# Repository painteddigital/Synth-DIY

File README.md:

# Synth-DIY
Files to produce the circuits to produce the instruments to produce sweet sweet music.

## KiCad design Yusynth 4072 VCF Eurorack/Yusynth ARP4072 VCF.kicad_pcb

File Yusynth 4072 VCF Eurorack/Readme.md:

This repo isn't quite production ready. So don't send these boards off to get made unless you know what you're doing. The jacks are not currently routed properly but I hope to fix them. If you know how to use KiCad and can fix them up, by all means submit a PR.

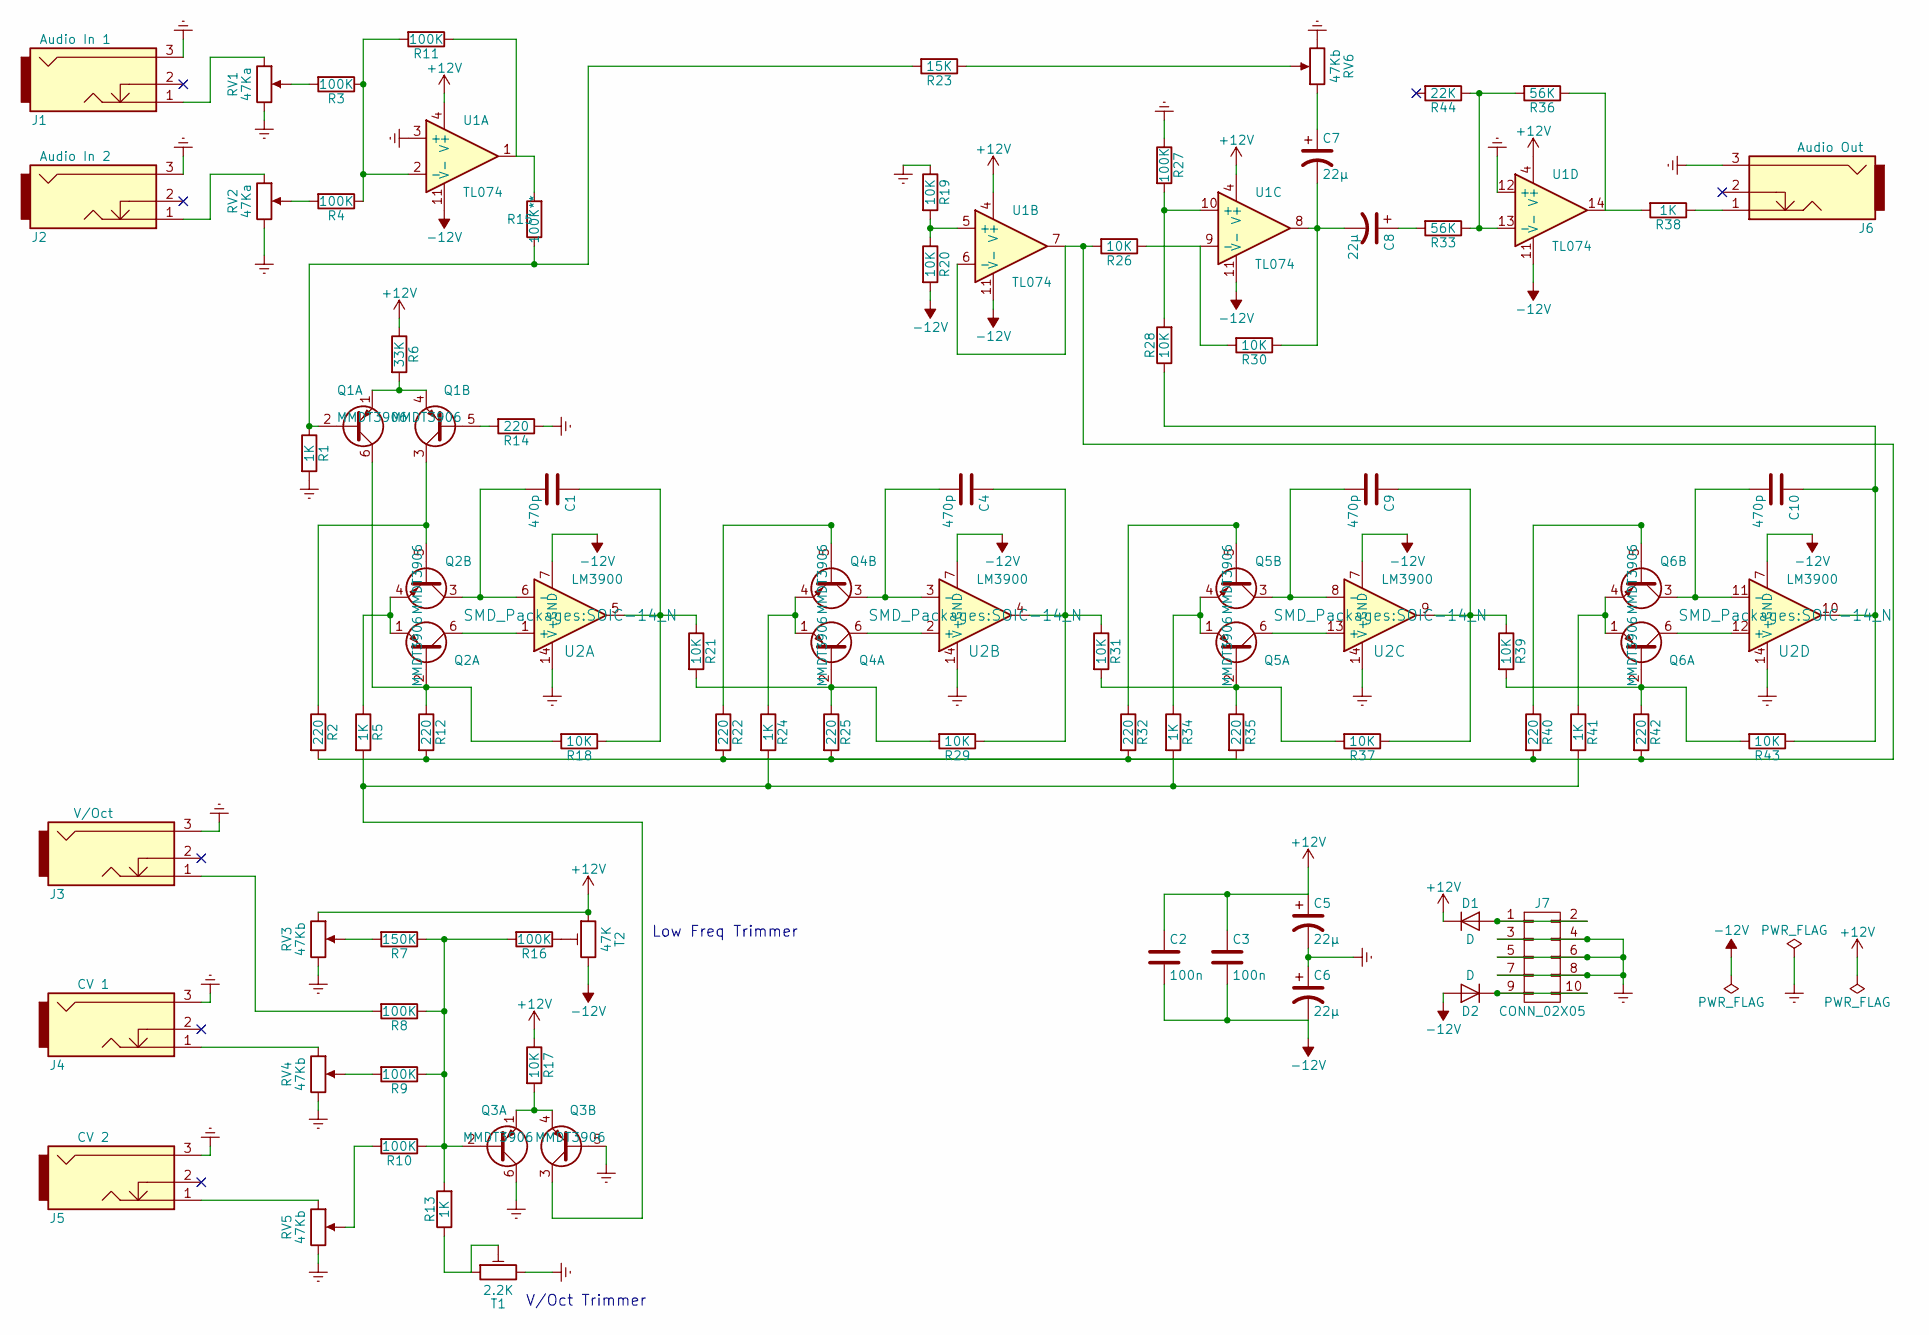
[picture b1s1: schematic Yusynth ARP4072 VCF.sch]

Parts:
C1, C4, C9, C10: 470p; C_Rect_L7.2mm_W4.5mm_P5.00mm_FKS2_FKP2_MKS2_MKP2
C2, C3: 100n; C_0603
C5, C6, C7, C8: 22µ; CP_Elec_5x5.7
D1, D2: D; D_SOD-123
J1: Audio In 1; THONKICONN
J2: Audio In 2; THONKICONN
J3: V/Oct; THONKICONN
J4: CV 1; THONKICONN
J5: CV 2; THONKICONN
J6: Audio Out; THONKICONN
J7: CONN_02X05; Pin_Header_Straight_2x05_Pitch2.54mm
Q1, Q2, Q3, Q4, Q5, Q6: MMDT3906; SOT-363_SC-70-6
R1, R5, R13, R24, R34, R38, R41: 1K; R_0603
R2, R12, R14, R22, R25, R32, R35, R40, R42: 220; R_0603
R3, R4, R8, R9, R10, R11, R16, R27: 100K; R_0603
R6: 33K; R_0603
R7: 150K; R_0603
R15: 100K**; R_0603
R17, R18, R19, R20, R21, R26, R28, R29, R30, R31, R37, R39, R43: 10K; R_0603
R23: 15K; R_0603
R33, R36: 56K; R_0603
R44: 22K; R_0603
RV1, RV2: 47Ka; Potentiometer_Alps_RK09L_Sleve_Single_Horizontal
RV3, RV4, RV5, RV6: 47Kb; Potentiometer_Alps_RK09L_Sleve_Single_Horizontal
T1: 2.2K; Potentiometer_Trimmer_Bourns_3296W
T2: 47K; Potentiometer_Trimmer_Bourns_3296W
U1: TL074; SOIC-14_N
U2: LM3900; SOIC-14_N

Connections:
+12V: C2.1, C3.1, C5.1, D1.1 (K), R6.1, R17.1, RV3.1, T2.1, U1.4 (V+)
-12V: C2.2, C3.2, C6.2, D2.2 (A), R20.2, T2.3, U1.11 (V-), U2.7 (GND)
Earth: C5.2, C6.1, J1.3, J2.3, J3.3, J4.3, J5.3, J6.3, J7.3, J7.4, J7.5, J7.6, J7.7, J7.8, Q3.5 (B2), Q3.6 (C1), R1.2, R14.1, R19.1, R27.1, RV1.3, RV2.3, RV3.3, RV4.3, RV5.3, RV6.3, T1.3, U1.3 (+), U1.12 (+), U2.14 (V+)
unnamed: C1.1, R18.1, R21.1, U2.5
unnamed: C1.2, Q2.3 (C2), U2.6 (-)
unnamed: C4.1, R29.1, R31.1, U2.4
unnamed: C4.2, Q4.3 (C2), U2.3 (-)
unnamed: C7.1, RV6.1
unnamed: C7.2, C8.2, R30.1, U1.8
unnamed: C8.1, R33.2
unnamed: C9.1, R37.1, R39.1, U2.9
unnamed: C9.2, Q5.3 (C2), U2.8 (-)
unnamed: C10.1, R28.1, R43.1, U2.10
unnamed: C10.2, Q6.3 (C2), U2.11 (-)
unnamed: D1.2 (A), J7.1, J7.2
unnamed: D2.1 (K), J7.9, J7.10
unnamed: J1.1, RV1.1
unnamed: J2.1, RV2.1
unnamed: J3.1, R8.2
unnamed: J4.1, RV4.1
unnamed: J5.1, RV5.1
unnamed: J6.1, R38.1
unnamed: Q1.1 (E1), Q1.4 (E2), R6.2
unnamed: Q1.2 (B1), R1.1, R15.1, R23.2
unnamed: Q1.3 (C2), Q2.5 (B2), R2.1
unnamed: Q1.5 (B2), R14.2
unnamed: Q1.6 (C1), Q2.2 (B1), R12.1, R18.2
unnamed: Q2.1 (E1), Q2.4 (E2), R5.1
unnamed: Q2.6 (C1), U2.1 (+)
unnamed: Q3.1 (E1), Q3.4 (E2), R17.2
unnamed: Q3.2 (B1), R7.1, R8.1, R9.1, R10.1, R13.2, R16.2
unnamed: Q3.3 (C2), R5.2, R24.2, R34.2, R41.2
unnamed: Q4.1 (E1), Q4.4 (E2), R24.1
unnamed: Q4.2 (B1), R21.2, R25.1, R29.2
unnamed: Q4.5 (B2), R22.1
unnamed: Q4.6 (C1), U2.2 (+)
unnamed: Q5.1 (E1), Q5.4 (E2), R34.1
unnamed: Q5.2 (B1), R31.2, R35.1, R37.2
unnamed: Q5.5 (B2), R32.1
unnamed: Q5.6 (C1), U2.13 (+)
unnamed: Q6.1 (E1), Q6.4 (E2), R41.1
unnamed: Q6.2 (B1), R39.2, R42.1, R43.2
unnamed: Q6.5 (B2), R40.1
unnamed: Q6.6 (C1), U2.12 (+)
unnamed: R3.2, RV1.2
unnamed: R4.2, RV2.2
unnamed: R7.2, RV3.2
unnamed: R9.2, RV4.2
unnamed: R10.2, RV5.2
unnamed: R11.1, R15.2, U1.1
unnamed: R3.1, R4.1, R11.2, U1.2 (-)
unnamed: R2.2, R12.2, R22.2, R25.2, R26.2, R32.2, R35.2, R40.2, R42.2, U1.6 (-), U1.7
unnamed: R13.1, T1.1, T1.2
unnamed: R16.1, T2.2
unnamed: R19.2, R20.1, U1.5 (+)
unnamed: R23.1, RV6.2
unnamed: R26.1, R30.2, U1.9 (-)
unnamed: R27.2, R28.2, U1.10 (+)
unnamed: R33.1, R36.2, R44.1, U1.13 (-)
unnamed: R36.1, R38.2, U1.14

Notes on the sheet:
V/Oct Trimmer
Low Freq Trimmer

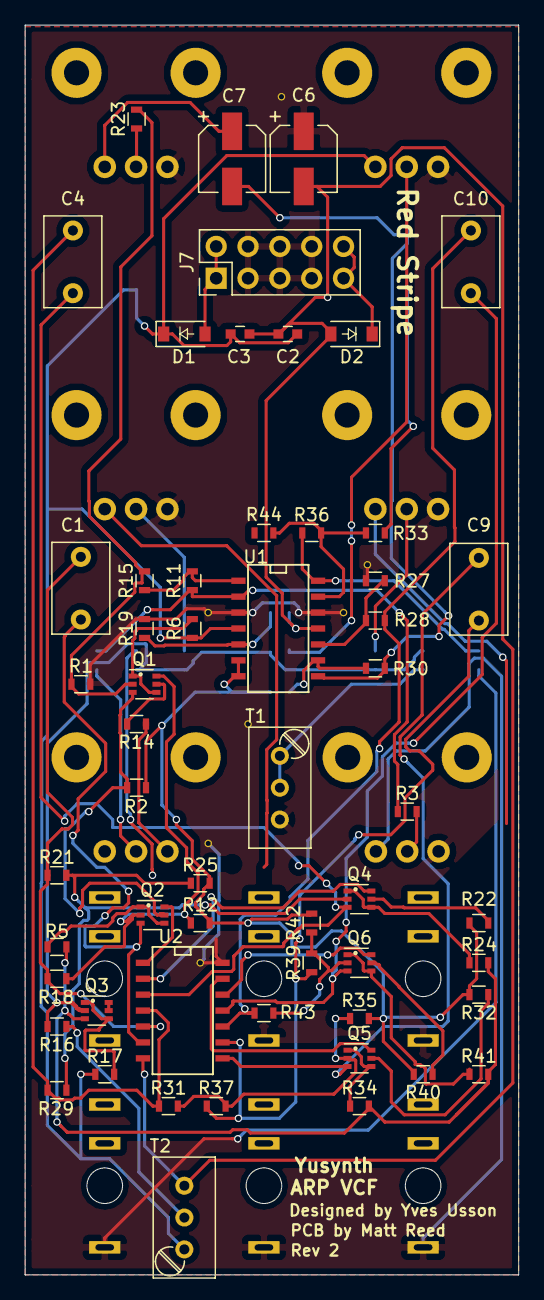
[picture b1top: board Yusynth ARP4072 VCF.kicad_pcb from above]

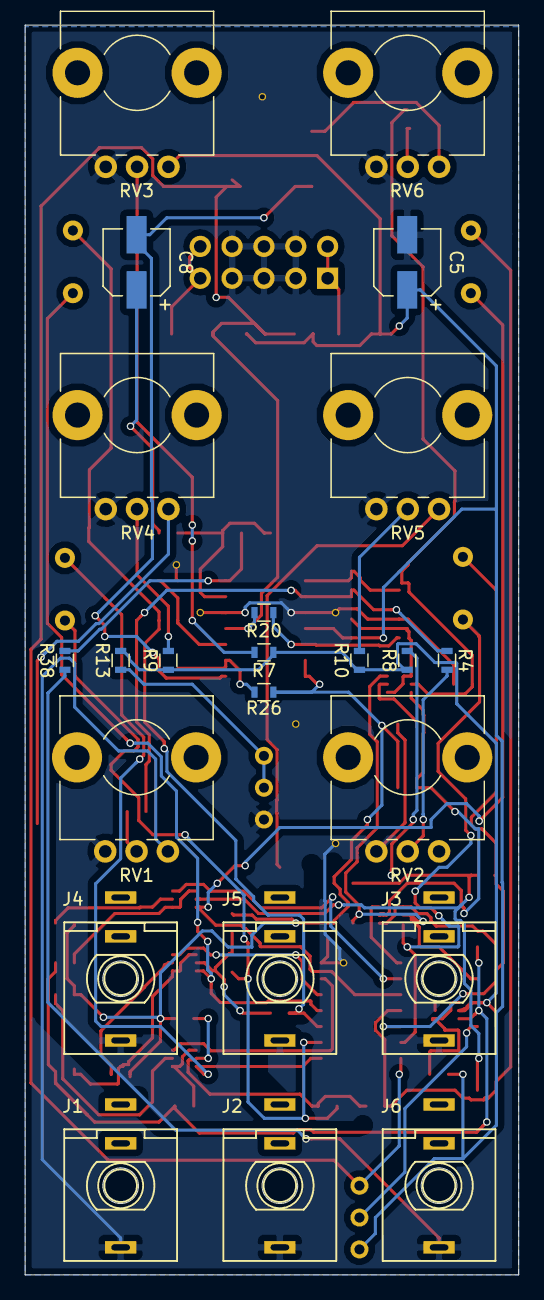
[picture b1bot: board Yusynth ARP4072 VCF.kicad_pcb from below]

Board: 2 copper layers, 39.4 x 99.7 mm, 79 parts (23 on the bottom side), 60 nets.

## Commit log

2017-10-31 Initial Commit. Adding Yusynth ARP VCF
2017-11-01 Fixed LM3900 pin mapping. File cleanup
2017-11-23 fixed power routing to LM3900
2017-11-23 Changed dual-gang pot to single gang for easier sourcing. Rotated pot footprints
2017-11-23 Added a separate schematic for dual-gang potentiometer
2017-11-23 Repositioned components for better grouping
2017-11-24 Trace updates
2017-11-24 Finished tracks and vias with no DRC errors.
2017-11-24 Minor text tweaks
2017-11-24 Added Ambika Case files
2017-11-25 Fixed some surprise DRC complaints
2017-12-03 Added holes in Thonkiconns, Resized for 100mm cuts, Rewired board
2017-12-10 Minor corrections
2018-01-28 Added fixed thonkiconn library and schematic PDF
2018-01-28 updated board to use corrected thonkiconn lib. Wiring incomplete.
2018-01-28 added front panel file for pcb manufacture
2018-01-28 added gerber files, kicad project file for panel
